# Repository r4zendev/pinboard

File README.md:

# pinboard

A 24-key unibody keyboard built for chorded typing with the [Pinchord](https://grahp.dev/pinchord) layout.

Pinchord is a chording system where you press a few keys at the same time to spell whole words instead of tapping them out letter by letter. The keys are split into three groups: the left fingers handle the start of a word, the thumbs and right index do the vowels, and the right fingers finish it off.

## Specs

- Support for both Kailh Choc v1 and v2 switches, with both hand-soldering and hotswap sockets supported
- Direct wiring (no diodes) with the help of using RP2040-Zero's pad pins on the back of the board
- Extremely cheap budget build

## Building one

Send the gerbers (see the releases page) off to your fab of choice. Once the boards are there, solder on the RP2040-Zero and optionally the hotswap sockets, then snap in your switches and keycaps.

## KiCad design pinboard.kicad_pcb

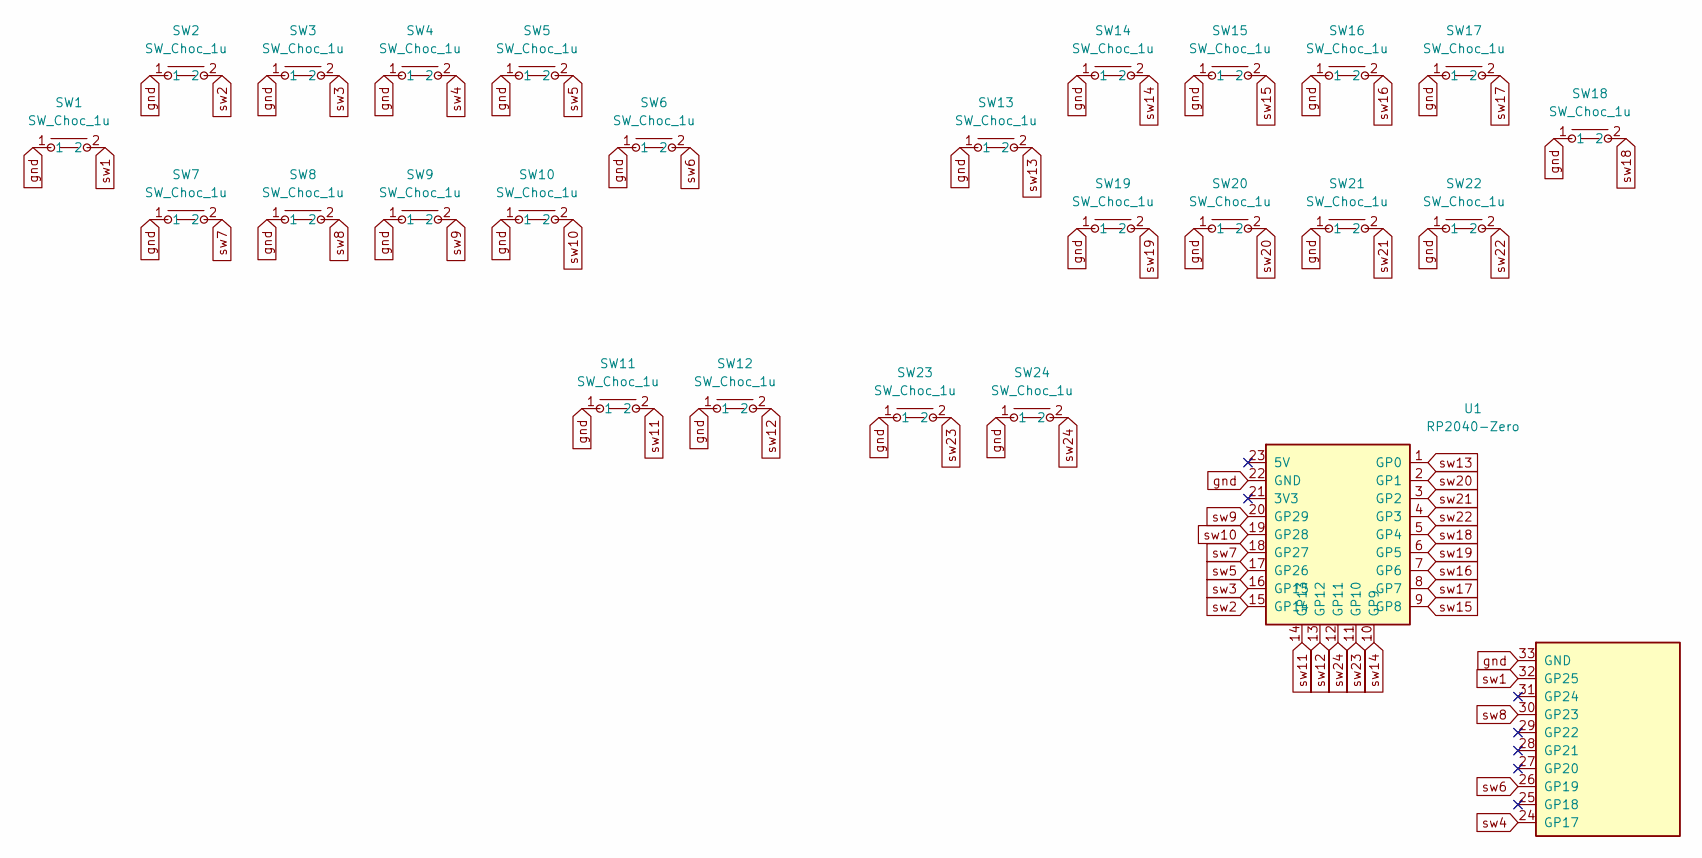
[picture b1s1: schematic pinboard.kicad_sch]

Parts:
SW1, SW2, SW3, SW4, SW5, SW6, SW7, SW8, SW9, SW10, SW11, SW12, SW13, SW14, SW15, SW16, SW17, SW18, SW19, SW20, SW21, SW22, SW23, SW24: SW_Choc_1u; SW_Choc_v1v2_1u_Solder_Hotswap
U1: RP2040-Zero; RP2040-Zero_THT_Pads

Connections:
gnd: SW1.1, SW2.1, SW3.1, SW4.1, SW5.1, SW6.1, SW7.1, SW8.1, SW9.1, SW10.1, SW11.1, SW12.1, SW13.1, SW14.1, SW15.1, SW16.1, SW17.1, SW18.1, SW19.1, SW20.1, SW21.1, SW22.1, SW23.1, SW24.1, U1.22 (GND), U1.33 (GND)
sw1: SW1.2, U1.32 (GP25)
sw2: SW2.2, U1.15 (GP14)
sw3: SW3.2, U1.16 (GP15)
sw4: SW4.2, U1.24 (GP17)
sw5: SW5.2, U1.17 (GP26)
sw6: SW6.2, U1.26 (GP19)
sw7: SW7.2, U1.18 (GP27)
sw8: SW8.2, U1.30 (GP23)
sw9: SW9.2, U1.20 (GP29)
sw10: SW10.2, U1.19 (GP28)
sw11: SW11.2, U1.14 (GP13)
sw12: SW12.2, U1.13 (GP12)
sw13: SW13.2, U1.1 (GP0)
sw14: SW14.2, U1.10 (GP9)
sw15: SW15.2, U1.9 (GP8)
sw16: SW16.2, U1.7 (GP6)
sw17: SW17.2, U1.8 (GP7)
sw18: SW18.2, U1.5 (GP4)
sw19: SW19.2, U1.6 (GP5)
sw20: SW20.2, U1.2 (GP1)
sw21: SW21.2, U1.3 (GP2)
sw22: SW22.2, U1.4 (GP3)
sw23: SW23.2, U1.11 (GP10)
sw24: SW24.2, U1.12 (GP11)

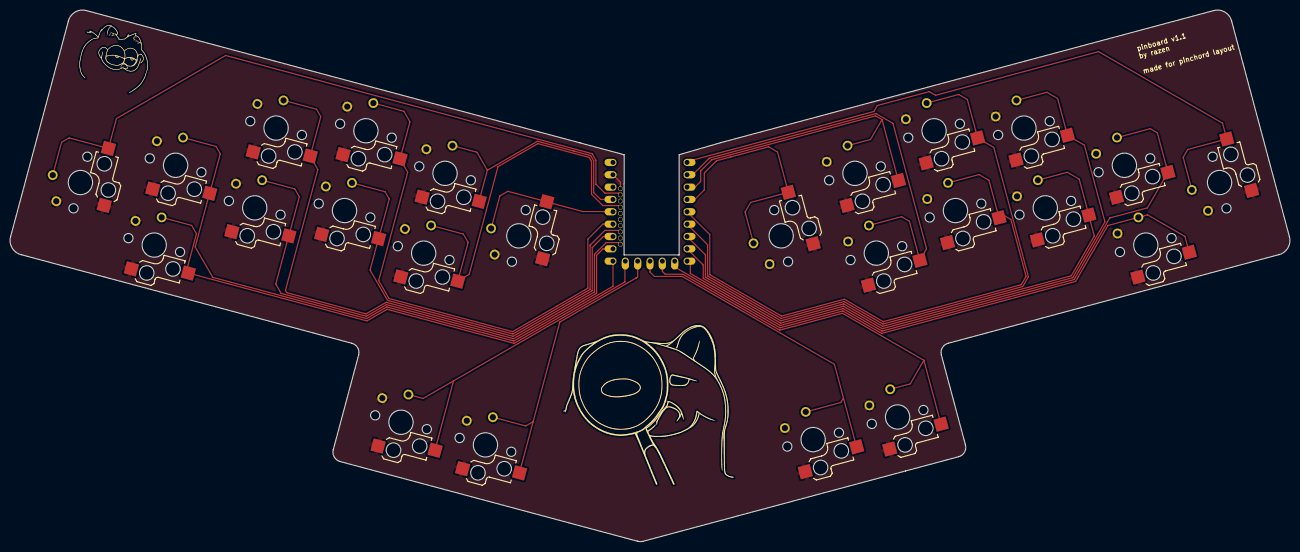
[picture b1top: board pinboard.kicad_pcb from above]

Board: 2 copper layers, 263.4 x 109.4 mm, 25 parts (0 on the bottom side), 25 nets.

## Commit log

2026-05-28 init
2026-05-28 add readme
2026-05-28 add link to releases
2026-05-29 v1.1
2026-05-29 update preview image and readme
